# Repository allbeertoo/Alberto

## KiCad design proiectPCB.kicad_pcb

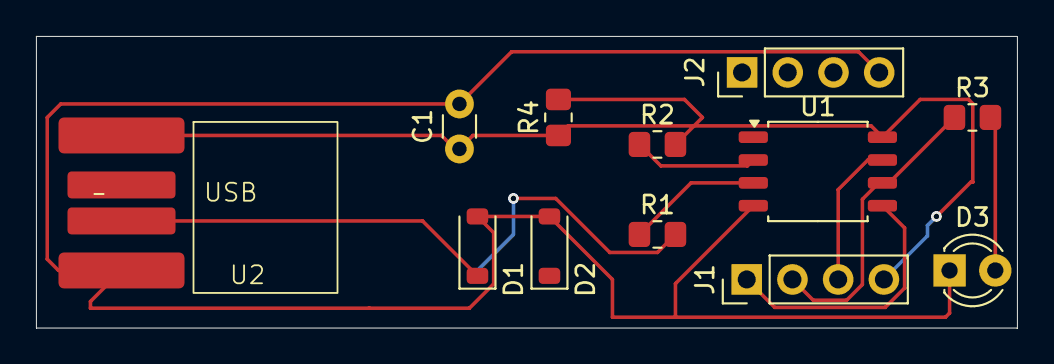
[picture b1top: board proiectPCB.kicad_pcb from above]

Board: 2 copper layers, 54.5 x 16.2 mm, 12 parts (0 on the bottom side), 11 nets.

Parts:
C1: 100n; C_Disc_D3.0mm_W1.6mm_P2.50mm
D1, D2: 3V6; D_SOD-123
D3: LED; LED_D3.0mm
J1, J2: Conn_01x04; PinHeader_1x04_P2.54mm_Vertical
R1, R2: 68R; R_0805_2012Metric_Pad1.20x1.40mm_HandSolder
R3: 330R; R_0805_2012Metric_Pad1.20x1.40mm_HandSolder
R4: 1k5; R_0805_2012Metric_Pad1.20x1.40mm_HandSolder
U1: ATtiny25-20S; SOIC-8_5.3x5.3mm_P1.27mm
U2: PCB_USB_connector

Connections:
+5V: C1.1, J1.4, R4.1, U1.8 (VCC), U2.1 (Vcc)
GND: C1.2, D1.2 (A), D2.2 (A), D3.1 (K), J2.4, U1.4 (GND), U2.4 (GND)
unnamed: D1.1 (K), R1.2, U2.3 (D-)
unnamed: D2.1 (K), R2.2, R4.2, U2.2 (D+)
unnamed: D3.2 (A), R3.2
unnamed: J1.1, U1.5 (AREF/PB0)
unnamed: J1.2, R3.1, U1.6 (PB1)
unnamed: J1.3, U1.7 (PB2)
unnamed: J2.1, U1.1 (~RESET/PB5)
unnamed: R2.1, U1.2 (XTAL1/PB3)
unnamed: R1.1, U1.3 (XTAL2/PB4)
